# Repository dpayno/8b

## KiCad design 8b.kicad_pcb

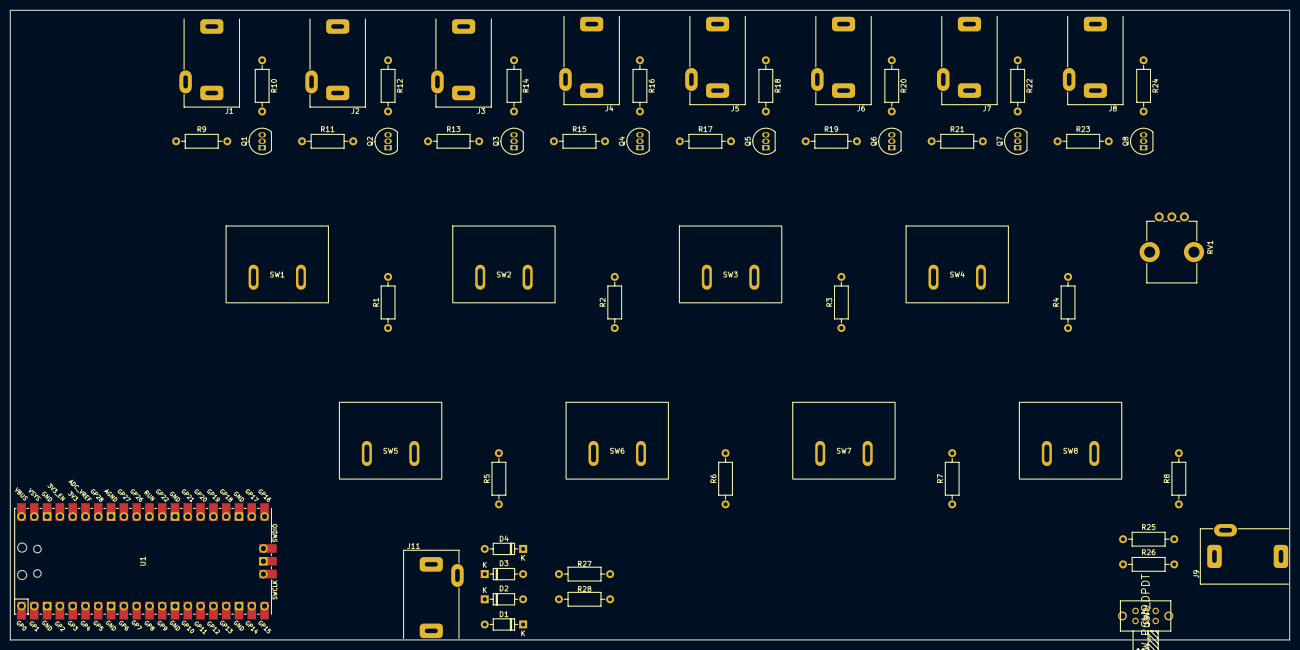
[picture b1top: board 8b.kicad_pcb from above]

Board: 2 copper layers, 254.0 x 125.0 mm, 61 parts (0 on the bottom side), 39 nets, no tracks yet.

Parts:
D1, D2, D3, D4: 1N4148; D_DO-35_SOD27_P7.62mm_Horizontal
J1, J2, J3, J4, J5, J6, J7, J8: AudioJack2; Jack_3.5mm_QingPu_WQP-PJ302M_Horizontal
J9, J11: AudioJack3; Jack_3.5mm_QingPu_WQP-PJ302M_Horizontal
Q1, Q2, Q3, Q4, Q5, Q6, Q7, Q8: 2N3904; TO-92_Inline
R1, R2, R3, R4, R5, R6, R7, R8, R10, R12, R14, R16, R18, R20, R22, R24: 10k; R_Axial_DIN0207_L6.3mm_D2.5mm_P10.16mm_Horizontal
R9, R11, R13, R15, R17, R19, R21, R23: 1k; R_Axial_DIN0207_L6.3mm_D2.5mm_P10.16mm_Horizontal
R25, R26: 47; R_Axial_DIN0207_L6.3mm_D2.5mm_P10.16mm_Horizontal
R27, R28: 4k7; R_Axial_DIN0207_L6.3mm_D2.5mm_P10.16mm_Horizontal
RV1: R_Potentiometer; Potentiometer_Bourns_PTV09A-1_Single_Vertical
SW1, SW2, SW3, SW4, SW5, SW6, SW7, SW8: SW_Push; sanwa-obsf-30-g
SW9: SW_Push_DPDT; EG2211
U1: Pico; RPi_Pico_SMD_TH

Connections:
+3.3V: D1.1 (K), D4.1 (K), R1.1, R2.1, R3.1, R4.1, R5.1, R6.1, R7.1, R8.1, R25.1, R27.2, R28.1, RV1.3, U1.36 (3V3)
+5V: R10.1, R12.1, R14.1, R16.1, R18.1, R20.1, R22.1, R24.1, U1.40 (VBUS)
/AN1: RV1.2, U1.32 (GPIO27_ADC1)
/IN1: R1.2, SW1.2, U1.9 (GPIO6)
/IN2: R2.2, SW2.2, U1.10 (GPIO7)
/IN3: R3.2, SW3.2, U1.11 (GPIO8)
/IN4: R4.2, SW4.2, U1.12 (GPIO9)
/IN5: R5.2, SW5.2, U1.14 (GPIO10)
/IN6: R6.2, SW6.2, U1.15 (GPIO11)
/IN7: R7.2, SW7.2, U1.16 (GPIO12)
/IN8: R8.2, SW8.2, U1.17 (GPIO13)
/MIDI_OUT: R26.1, U1.1 (GPIO0)
/OUT1: R9.1, U1.19 (GPIO14)
/OUT2: R11.1, U1.20 (GPIO15)
/OUT3: R13.1, U1.21 (GPIO16)
/OUT4: R15.1, U1.22 (GPIO17)
/OUT5: R17.1, U1.24 (GPIO18)
/OUT6: R19.1, U1.25 (GPIO19)
/OUT7: R21.1, U1.26 (GPIO20)
/OUT8: R23.1, U1.27 (GPIO21)
/SCL: D1.2 (A), D2.1 (K), R27.1, U1.7 (GPIO5)
/SDA: D3.1 (K), D4.2 (A), J11.T, R28.2, U1.6 (GPIO4)
GND: D2.2 (A), D3.2 (A), J1.S, J2.S, J3.S, J4.S, J5.S, J6.S, J7.S, J8.S, J9.S, J11.S, Q1.1 (E), Q2.1 (E), Q3.1 (E), Q4.1 (E), Q5.1 (E), Q6.1 (E), Q7.1 (E), Q8.1 (E), RV1.1, SW1.1, SW2.1, SW3.1, SW4.1, SW5.1, SW6.1, SW7.1, SW8.1, U1.3 (GND), U1.8 (GND), U1.13 (GND), U1.18 (GND), U1.23 (GND), U1.28 (GND), U1.33 (AGND), U1.38 (GND), U1.42 (GND)
unnamed: Q1.2 (B), R9.2
unnamed: J1.T, Q1.3 (C), R10.2
unnamed: Q2.2 (B), R11.2
unnamed: J2.T, Q2.3 (C), R12.2
unnamed: Q3.2 (B), R13.2
unnamed: J3.T, Q3.3 (C), R14.2
unnamed: Q4.2 (B), R15.2
unnamed: J4.T, Q4.3 (C), R16.2
unnamed: Q5.2 (B), R17.2
unnamed: J5.T, Q5.3 (C), R18.2
unnamed: Q6.2 (B), R19.2
unnamed: J6.T, Q6.3 (C), R20.2
unnamed: Q7.2 (B), R21.2
unnamed: J7.T, Q7.3 (C), R22.2
unnamed: Q8.2 (B), R23.2
unnamed: J8.T, Q8.3 (C), R24.2

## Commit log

2023-06-13 Add gitignore
2023-06-13 Add i2c interface & MIDI interface
2023-06-14 Update schem
2023-06-14 Update submodule
2023-06-14 Remove submodules
2023-06-14 Update submodules & schematic
2023-06-14 Add Raspberry Pi Pico as control module
2023-06-15 Update some footprints
2023-06-16 Add missing footprints
2023-06-16 Update footprint components
2023-06-16 Layout draft
